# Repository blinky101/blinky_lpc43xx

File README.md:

# LPC43xx Example Project: Blinky

Simple Hello World-like blinky programs for the LPC43xx platform.
This repositories contains three blinky programs, in increasing order of complexity / abstraction level:

1. [bare-metal](/bare-metal): A blinky program in one file, with no dependencies at all.
2. [basic](/basic): A proper but very basic c program, where the low-level stuff is in separate functions.
3. [cpm](/cpm/): Using CPM as c package manager: reuseable dependencies are in separate repositories.

Extras:
* [dual_core](/dual_core/): Uses both the cortex-M4 and the cortex-M0 cores, blinking two LEDS independently.
* [cpm_bootloader](/cpm_bootloader/): Same as [cpm](/cpm/), but used in combination with a custom bootloader.

See [the blinky website](https://blinky101.github.io/blinky_lpc43xx/) and the per-project *README* files for more information.

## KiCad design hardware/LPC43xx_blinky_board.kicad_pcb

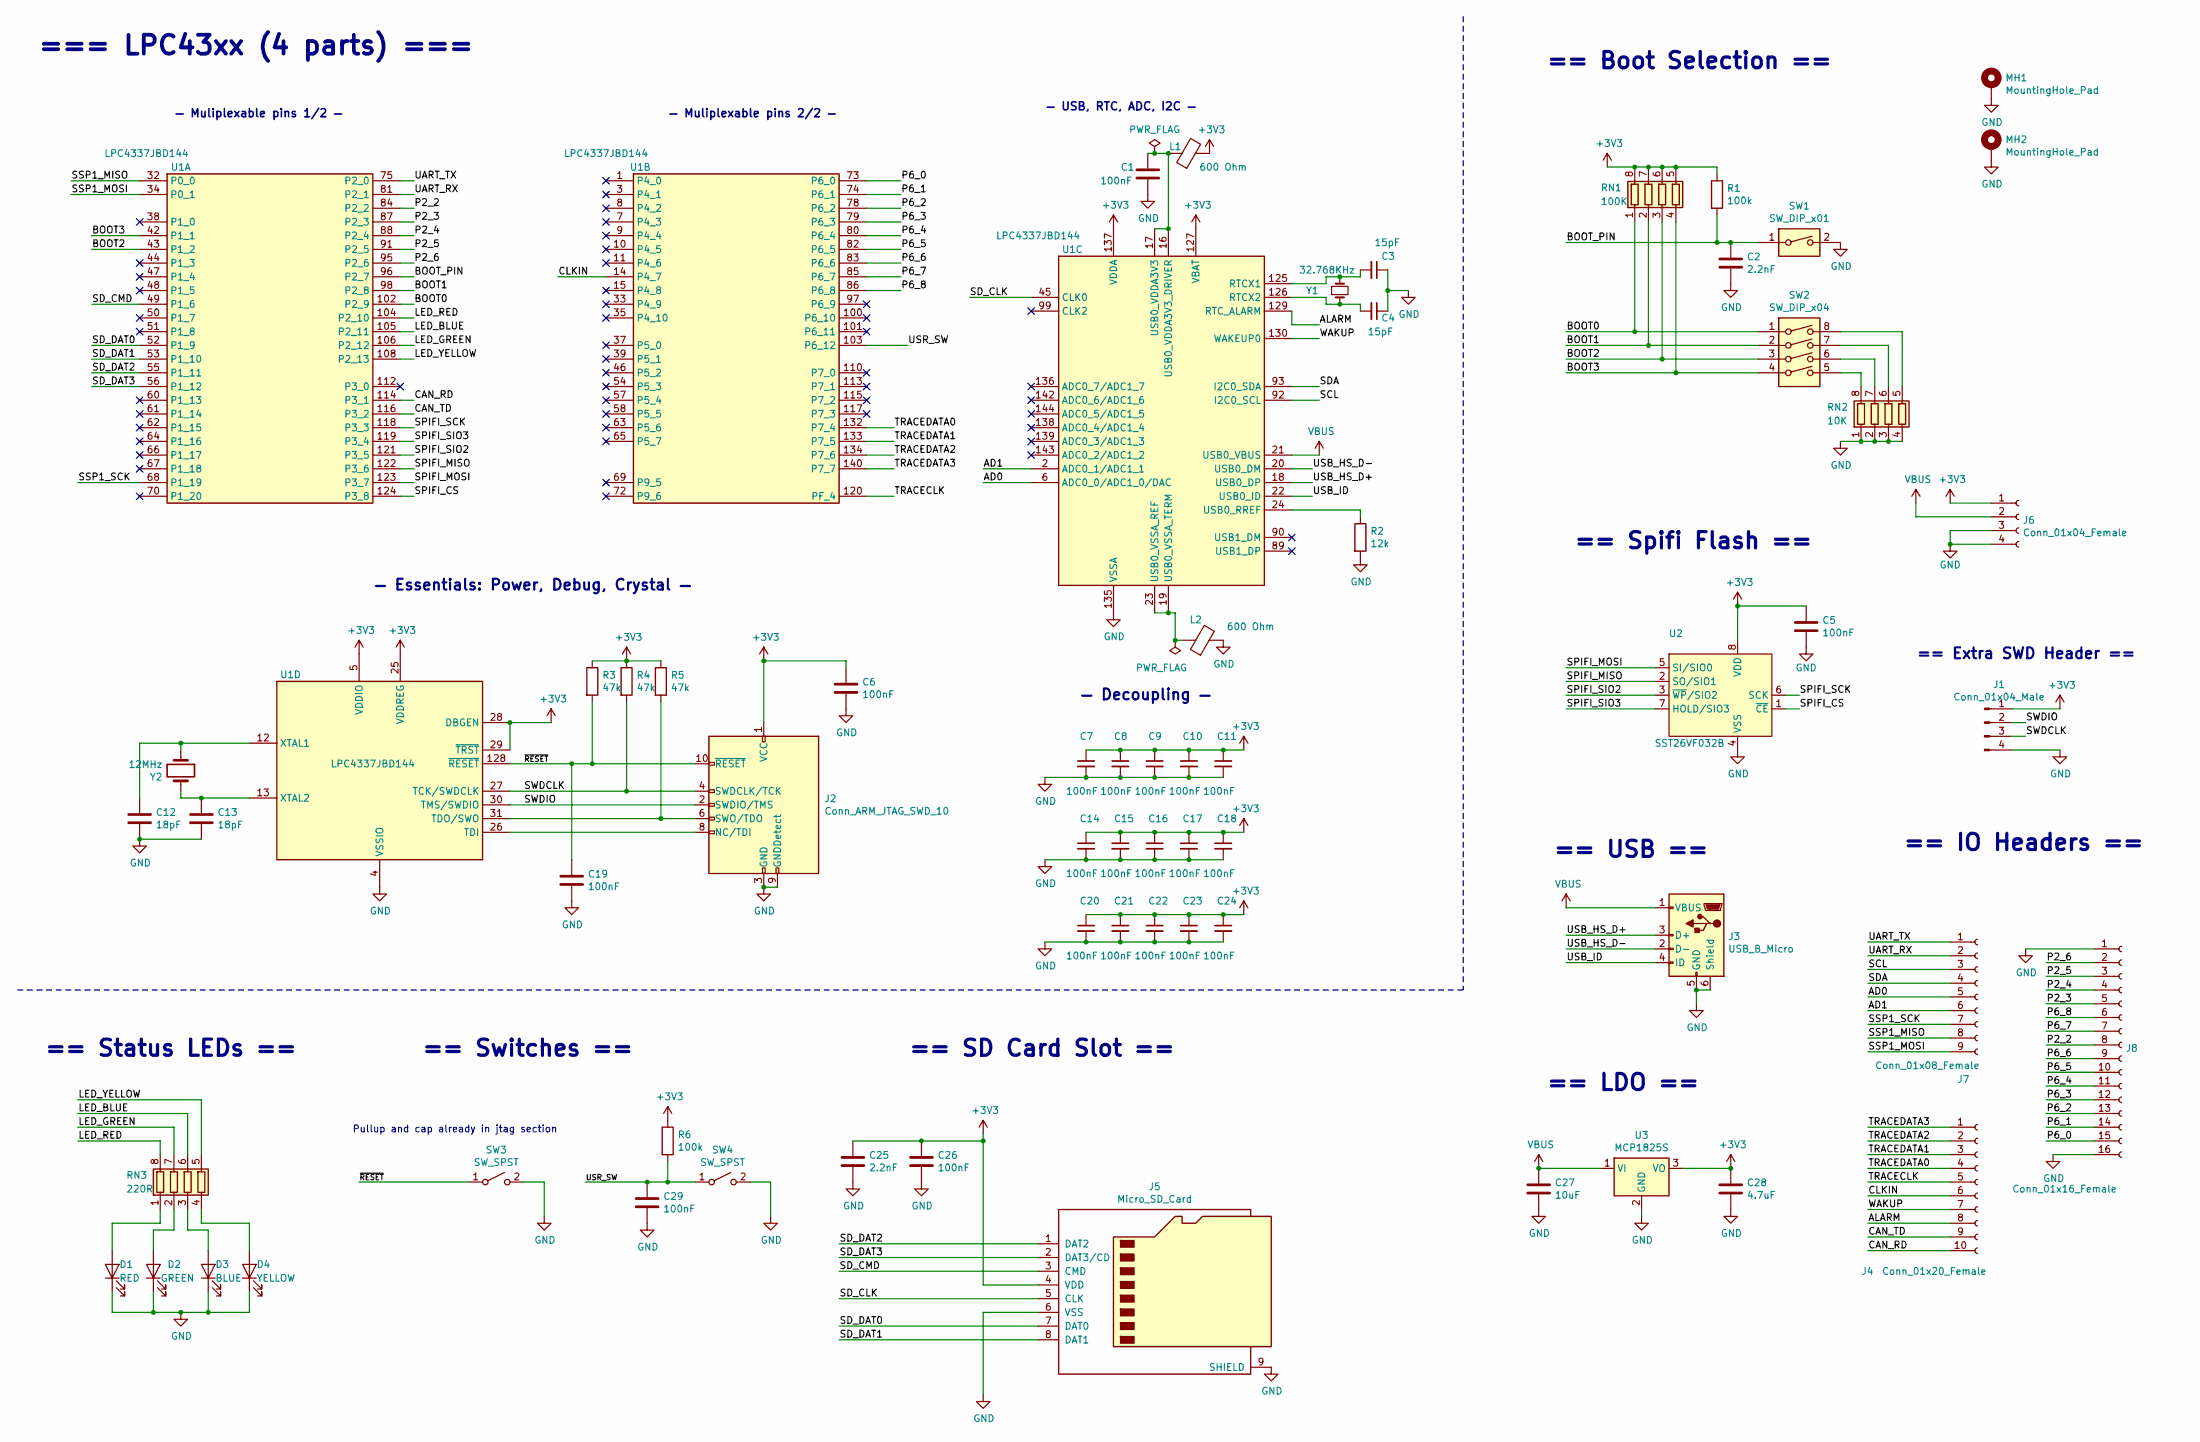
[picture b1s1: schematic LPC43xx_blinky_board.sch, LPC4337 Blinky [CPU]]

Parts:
C1, C5, C6, C7, C8, C9, C10, C11, C14, C15, C16, C17, C18, C19, C20, C21, C22, C23, C24, C26, C29: 100nF; C_0402_1005Metric
C2, C25: 2.2nF; C_0402_1005Metric
C3, C4: 15pF; C_0402_1005Metric
C12, C13: 18pF; C_0402_1005Metric
C27: 10uF; C_0805_2012Metric
C28: 4.7uF; C_0805_2012Metric
D1: RED; LED_0603_1608Metric
D2: GREEN; LED_0603_1608Metric
D3: BLUE; LED_0603_1608Metric
D4: YELLOW; LED_0603_1608Metric
J1: Conn_01x04_Male; PinHeader_1x04_P2.54mm_Horizontal
J2: Conn_ARM_JTAG_SWD_10; PinHeader_2x05_P1.27mm_Vertical_SMD
J3: USB_B_Micro; USB_Micro-B_Molex_47346-0001
J4: Conn_01x20_Female; PinSocket_1x10_P2.54mm_Vertical
J5: Micro_SD_Card; microSD_HC_Wuerth_693072010801
J6: Conn_01x04_Female; PinSocket_1x04_P2.54mm_Vertical
J7: Conn_01x08_Female; PinSocket_1x09_P2.54mm_Vertical
J8: Conn_01x16_Female; PinSocket_1x16_P2.54mm_Vertical
L1: 600 Ohm; R_0402_1005Metric
L2: 600 Ohm; R_0402_1005Metric; Manufacturer PartNo. BLM15HG601SN1D
MH1, MH2: MountingHole_Pad; MountingHole_3.2mm_M3_Pad_Via
R1, R6: 100k; R_0402_1005Metric
R2: 12k; R_0402_1005Metric
R3, R4, R5: 47k; R_0402_1005Metric
RN1: 100K; R_Array_Convex_4x0402
RN2: 10K; R_Array_Convex_4x0402
RN3: 220R; R_Array_Convex_4x0402
SW1: SW_DIP_x01; SW_DIP_SPSTx01_Slide_Omron_A6S-110x_W8.9mm_P2.54mm
SW2: SW_DIP_x04; SW_DIP_SPSTx04_Slide_Omron_A6S-410x_W8.9mm_P2.54mm
SW3, SW4: SW_SPST; SW_SPST_EVQPE1
U1: LPC4337JBD144; LQFP-144_20x20mm_P0.5mm
U2: SST26VF032B; SOIC-8_3.9x4.9mm_P1.27mm
U3: MCP1825S; SOT-223-3_TabPin2
Y1: 32.768KHz; Crystal_SMD_Abracon_ABS07-2Pin_3.6x1.9mm
Y2: 12MHz; Crystal_SMD_TXC_7A-2Pin_5.0x3.2mm

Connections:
+3V3: C5.1, C6.1, C7.1, C8.1, C9.1, C10.1, C11.1, C14.1, C15.1, C16.1, C17.1, C18.1, C20.1, C21.1, C22.1, C23.1, C24.1, C25.1, C26.1, C28.1, J1.1, J2.1 (VCC), J5.4 (VDD), J6.1, L1.2, R1.1, R3.1, R4.1, R5.1, R6.1, RN1.5 (R4.2), RN1.6 (R3.2), RN1.7 (R2.2), RN1.8 (R1.2), U1.5 (VDDIO), U1.25 (VDDREG), U1.28 (DBGEN), U1.29 (~TRST), U1.36 (VDDIO), U1.41 (VDDIO), U1.59 (VDDREG), U1.71 (VDDIO), U1.77 (VDDIO), U1.94 (VDDREG), U1.107 (VDDIO), U1.111 (VDDIO), U1.127 (VBAT), U1.131 (VDDREG), U1.137 (VDDA), U1.141 (VDDIO), U2.8 (VDD), U3.3 (VO)
/AD0: J7.5, U1.6 (ADC0_0/ADC1_0/DAC)
/AD1: J7.6, U1.2 (ADC0_1/ADC1_1)
/ALARM: J4.8, U1.129 (RTC_ALARM)
/BOOT0: RN1.1 (R1.1), SW2.1, U1.102 (P2_9)
/BOOT1: RN1.2 (R2.1), SW2.2, U1.98 (P2_8)
/BOOT2: RN1.3 (R3.1), SW2.3, U1.43 (P1_2)
/BOOT3: RN1.4 (R4.1), SW2.4, U1.42 (P1_1)
/BOOT_PIN: C2.1, R1.2, SW1.1, U1.96 (P2_7)
/CAN_RD: J4.10, U1.114 (P3_1)
/CAN_TD: J4.9, U1.116 (P3_2)
/CLKIN: J4.6, U1.14 (P4_7)
/LED_BLUE: RN3.6 (R3.2), U1.105 (P2_11)
/LED_GREEN: RN3.7 (R2.2), U1.106 (P2_12)
/LED_RED: RN3.8 (R1.2), U1.104 (P2_10)
/LED_YELLOW: RN3.5 (R4.2), U1.108 (P2_13)
/P2_2: J8.8, U1.84 (P2_2)
/P2_3: J8.5, U1.87 (P2_3)
/P2_4: J8.4, U1.88 (P2_4)
/P2_5: J8.3, U1.91 (P2_5)
/P2_6: J8.2, U1.95 (P2_6)
/P6_0: J8.15, U1.73 (P6_0)
/P6_1: J8.14, U1.74 (P6_1)
/P6_2: J8.13, U1.78 (P6_2)
/P6_3: J8.12, U1.79 (P6_3)
/P6_4: J8.11, U1.80 (P6_4)
/P6_5: J8.10, U1.82 (P6_5)
/P6_6: J8.9, U1.83 (P6_6)
/P6_7: J8.7, U1.85 (P6_7)
/P6_8: J8.6, U1.86 (P6_8)
/SCL: J7.3, U1.92 (I2C0_SCL)
/SDA: J7.4, U1.93 (I2C0_SDA)
/SD_CLK: J5.5 (CLK), U1.45 (CLK0)
/SD_CMD: J5.3 (CMD), U1.49 (P1_6)
/SD_DAT0: J5.7 (DAT0), U1.52 (P1_9)
/SD_DAT1: J5.8 (DAT1), U1.53 (P1_10)
/SD_DAT2: J5.1 (DAT2), U1.55 (P1_11)
/SD_DAT3: J5.2 (DAT3/CD), U1.56 (P1_12)
/SPIFI_CS: U1.124 (P3_8), U2.1 (~CE)
/SPIFI_MISO: U1.122 (P3_6), U2.2 (SO/SIO1)
/SPIFI_MOSI: U1.123 (P3_7), U2.5 (SI/SIO0)
/SPIFI_SCK: U1.118 (P3_3), U2.6 (SCK)
/SPIFI_SIO2: U1.121 (P3_5), U2.3 (~WP~/SIO2)
/SPIFI_SIO3: U1.119 (P3_4), U2.7 (HOLD/SIO3)
/SSP1_MISO: J7.8, U1.32 (P0_0)
/SSP1_MOSI: J7.9, U1.34 (P0_1)
/SSP1_SCK: J7.7, U1.68 (P1_19)
/SWDCLK: J1.3, J2.4 (SWDCLK/TCK), R4.2, U1.27 (TCK/SWDCLK)
/SWDIO: J1.2, J2.2 (SWDIO/TMS), U1.30 (TMS/SWDIO)
/TRACECLK: J4.5, U1.120 (PF_4)
/TRACEDATA0: J4.4, U1.132 (P7_4)
/TRACEDATA1: J4.3, U1.133 (P7_5)
/TRACEDATA2: J4.2, U1.134 (P7_6)
/TRACEDATA3: J4.1, U1.140 (P7_7)
/UART_RX: J7.2, U1.81 (P2_1)
/UART_TX: J7.1, U1.75 (P2_0)
/USB_HS_D+: J3.3 (D+), U1.18 (USB0_DP)
/USB_HS_D-: J3.2 (D-), U1.20 (USB0_DM)
/USB_ID: J3.4 (ID), U1.22 (USB0_ID)
/USR_SW: C29.1, R6.2, SW4.1 (A), U1.103 (P6_12)
/WAKUP: J4.7, U1.130 (WAKEUP0)
/~RESET: C19.1, J2.10 (~RESET~), R3.2, SW3.1 (A), U1.128 (~RESET)
GND: C1.2, C2.2, C3.1, C4.1, C5.2, C6.2, C7.2, C8.2, C9.2, C10.2, C11.2, C12.2, C13.2, C14.2, C15.2, C16.2, C17.2, C18.2, C19.2, C20.2, C21.2, C22.2, C23.2, C24.2, C25.2, C26.2, C27.2, C28.2, C29.2, D1.1 (K), D2.1 (K), D3.1 (K), D4.1 (K), J1.4, J2.3 (GND), J2.5 (GND), J2.9 (GNDDetect), J3.5 (GND), J3.6 (Shield), J5.6 (VSS), J5.9 (SHIELD), J6.3, J6.4, J8.1, J8.16, L2.2, MH1.1, MH2.1, R2.2, RN2.1 (R1.1), RN2.2 (R2.1), RN2.3 (R3.1), RN2.4 (R4.1), SW1.2, SW3.2 (B), SW4.2 (B), U1.4 (VSSIO), U1.40 (VSSIO), U1.76 (VSSIO), U1.109 (VSSIO), U1.135 (VSSA), U2.4 (VSS), U3.2 (GND)
unnamed: C1.1, L1.1, U1.16 (USB0_VDDA3V3_DRIVER), U1.17 (USB0_VDDA3V3)
unnamed: C3.2, U1.125 (RTCX1), Y1.1
unnamed: C4.2, U1.126 (RTCX2), Y1.2
unnamed: C12.1, U1.12 (XTAL1), Y2.1
unnamed: C13.1, U1.13 (XTAL2), Y2.2
unnamed: D1.2 (A), RN3.1 (R1.1)
unnamed: D2.2 (A), RN3.2 (R2.1)
unnamed: D3.2 (A), RN3.3 (R3.1)
unnamed: D4.2 (A), RN3.4 (R4.1)
unnamed: J2.6 (SWO/TDO), R5.2, U1.31 (TDO/SWO)
unnamed: J2.8 (NC/TDI), U1.26 (TDI)
unnamed: L2.1, U1.19 (USB0_VSSA_TERM), U1.23 (USB0_VSSA_REF)
unnamed: R2.1, U1.24 (USB0_RREF)
unnamed: RN2.5 (R4.2), SW2.8
unnamed: RN2.6 (R3.2), SW2.7
unnamed: RN2.7 (R2.2), SW2.6
unnamed: RN2.8 (R1.2), SW2.5
VBUS: C27.1, J3.1 (VBUS), J6.2, U1.21 (USB0_VBUS), U3.1 (VI)

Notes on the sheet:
== Boot Selection ==
— Decoupling —
— Essentials: Power, Debug, Crystal —
— USB, RTC, ADC, I2C —
== Switches ==
== Spifi Flash ==
== Status LEDs ==
== SD Card Slot ==
=== LPC43xx (4 parts) ===
— Muliplexable pins 1/2 —
— Muliplexable pins 2/2 —
== USB ==
== LDO ==
== IO Headers ==
== Extra SWD Header ==
Pullup and cap already in jtag section

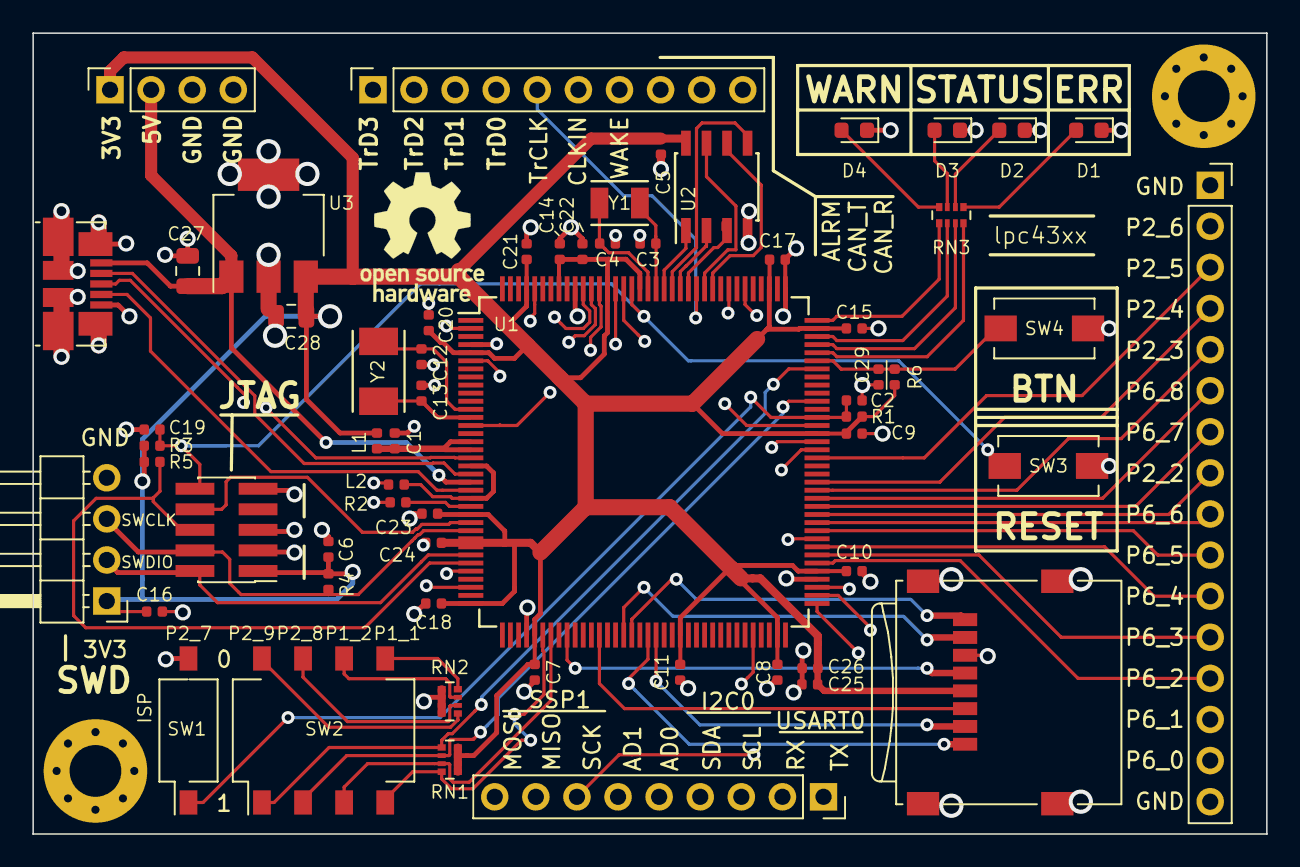
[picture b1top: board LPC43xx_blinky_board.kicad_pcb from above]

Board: 4 copper layers, 76.2 x 49.5 mm, 63 parts (0 on the bottom side), 81 nets.

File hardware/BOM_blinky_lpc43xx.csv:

,,,,,,,,,
Ref,Value,Qnty,Supplier and ref,Cmp name,Footprint,Description,Vendor,,
"C3, C4,",15pF,2,3019172,C_Small,Capacitor_SMD:C_0402_1005Metric,"Unpolarized capacitor, small symbol",,,
"C6, C2, C7, C29, C8, C9, C11, C10, C14, C15, C16, C18, C17, C20, C21, C22, C24, C23, C5, C1, C26, C19,",100nF,22,2627420,C,Capacitor_SMD:C_0402_1005Metric,Unpolarized capacitor,,,
"C13, C12,",18pF,2,2896333,C,Capacitor_SMD:C_0402_1005Metric,Unpolarized capacitor,,,
"C25,",2.2nF,1,2896351,C,Capacitor_SMD:C_0402_1005Metric,Unpolarized capacitor,,,
"C27,",10uF,1,2611941,C,Capacitor_SMD:C_0805_2012Metric,Unpolarized capacitor,,,
"C28,",4.7uF,1,9402160,C,Capacitor_SMD:C_0805_2012Metric,Unpolarized capacitor,,,
"D1,",RED,1,2322071,LED,LED_SMD:LED_0603_1608Metric,Light emitting diode,,,
"D2,",GREEN,1,2846585,LED,LED_SMD:LED_0603_1608Metric,Light emitting diode,,,
"D3,",BLUE,1,1328305,LED,LED_SMD:LED_0603_1608Metric,Light emitting diode,,,
"D4,",YELLOW,1,2103887,LED,LED_SMD:LED_0603_1608Metric,Light emitting diode,,,
"J2,",Conn_ARM_JTAG_SWD_10,1,2856426,Conn_ARM_JTAG_SWD_10,Connector_PinHeader_1.27mm:PinHeader_2x05_P1.27mm_Vertical_SMD,"Cortex Debug Connector, standard ARM Cortex-M SWD and JTAG interface",,,
"J3,",USB_B_Micro,1,1568026,USB_B_Micro,Connector_USB:USB_Micro-B_Molex_47346-0001,USB Micro Type B connector,,,
"J5,",Micro_SD_Card,1,2081364,Micro_SD_Card,Connector_Card:microSD_HC_Wuerth_693072010801,Micro SD Card Socket,,,
"L1, L2,",600 Ohm,2,2443223,Ferrite_Bead,Resistor_SMD:R_0402_1005Metric,Ferrite bead,,,
"R1, R6,",100k,2,2861833,R,Resistor_SMD:R_0402_1005Metric,Resistor,,,
"R2,",12k,1,2447104,R,Resistor_SMD:R_0402_1005Metric,Resistor,,,
"R5, R4, R3,",47k,3,2861831,R,Resistor_SMD:R_0402_1005Metric,Resistor,,,
"RN1,",100K,1,2060062,R_Pack04,Resistor_SMD:R_Array_Convex_4x0402,"4 resistor network, parallel topology, DIP package",,,
"RN2,",10K,1,2060058,R_Pack04,Resistor_SMD:R_Array_Convex_4x0402,"4 resistor network, parallel topology, DIP package",,,
"RN3,",220R,1,9235329,R_Pack04,Resistor_SMD:R_Array_Convex_4x0402,"4 resistor network, parallel topology, DIP package",,,
"SW1,",SW_DIP_x01,1,1960892,SW_DIP_x01,Button_Switch_SMD:SW_DIP_SPSTx01_Slide_Omron_A6S-110x_W8.9mm_P2.54mm,"1x DIP Switch, Single Pole Single Throw (SPST) switch, small symbol",,,
"SW2,",SW_DIP_x04,1,1960899,SW_DIP_x04,Button_Switch_SMD:SW_DIP_SPSTx04_Slide_Omron_A6S-410x_W8.9mm_P2.54mm,"4x DIP Switch, Single Pole Single Throw (SPST) switch, small symbol",,,
"SW3, SW4,",SW_SPST,2,2079522,SW_SPST,Button_Switch_SMD:SW_SPST_EVQPE1,Single Pole Single Throw (SPST) switch,,,
"U1,",LPC4337JBD144,1,2320720,LPC4337JBD144-JitterLib,Package_QFP:LQFP-144_20x20mm_P0.5mm,,,,
"U2,",SST26VF032B,1,2471177,SST26VF032B,Package_SO:SOIC-8_3.9x4.9mm_P1.27mm,Quad SPI Flash 4MB,,,
"U3,",MCP1825S,1,1578404,MCP1825S,Package_TO_SOT_SMD:SOT-223-3_TabPin2,"500 mA, Low-Voltage, Low Quiescent Current LDO Regulator, SOT-223, TO-220, TO-263",,,
"Y1,",32.768KHz,1,2101347,Crystal_Small,Jitter_Footprints:Crystal_SMD_Abracon_ABS07-2Pin_3.6x1.9mm,"Two pin crystal, small symbol",,,
"Y2,",12MHz,1,1841940,Crystal,Jitter_Footprints:Crystal_SMD_TXC_7A-2Pin_5.0x3.2mm,Two pin crystal,,,
"J1,",Conn_01x04_Male,1,,Conn_01x04_Male,Connector_PinHeader_2.54mm:PinHeader_1x04_P2.54mm_Horizontal,"Generic connector, single row, 01x04, script generated (kicad-library-utils/schlib/autogen/connector/)",,,
"J4,",Conn_01x20_Female,1,,Conn_01x10_Female,Connector_PinSocket_2.54mm:PinSocket_1x10_P2.54mm_Vertical,"Generic connector, single row, 01x10, script generated (kicad-library-utils/schlib/autogen/connector/)",,,
"J6,",Conn_01x04_Female,1,,Conn_01x04_Female,Connector_PinSocket_2.54mm:PinSocket_1x04_P2.54mm_Vertical,"Generic connector, single row, 01x04, script generated (kicad-library-utils/schlib/autogen/connector/)",,,
"J7,",Conn_01x08_Female,1,,Conn_01x09_Female,Connector_PinSocket_2.54mm:PinSocket_1x09_P2.54mm_Vertical,"Generic connector, single row, 01x09, script generated (kicad-library-utils/schlib/autogen/connector/)",,,
"J8,",Conn_01x16_Female,1,,Conn_01x16_Female,Connector_PinSocket_2.54mm:PinSocket_1x16_P2.54mm_Vertical,"Generic connector, single row, 01x16, script generated (kicad-library-utils/schlib/autogen/connector/)",,,

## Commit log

2016-08-29 First commit: simple CPM demo package
    A simple Hello World style blinky program for the LPC43xx platform
    as a CPM package.
    Only the M4 core is used. This is a very basic demo
    program to show how the library packages can be used.
    It depends on:
    * 43xx_m4_startup: startup code
2016-08-31 upgrade to openocd_tools 1.1
2016-09-01 Add CMake Toolchain file
2016-09-01 fix flash.cfg flusing
2016-09-26 Change ASM compiler from as to gcc
    This way you can use gcc switches
2016-09-26 link to system libraries, use gcc as linker
    This commit does not change how this example firmware project works,
    but makes it easier to build a more complex firmware on top of it:
    - link to libm, libc, libgcc. If you dou anything more than
    a very simple hello world program, you need this.
    - a few tweaks to the linker flags
2017-04-11 Interrupt-based version of blinky
    This version uses the systick timer interrupt instead of a blocking loop.
2017-04-11 Blinky demo: version for use with bootloader
    See the bootloader43xx_sdcard project on github for the bootloader.
2018-08-09 update dependencies to latest versions
2018-08-21 Fix cmake dependencies so that 'make flash' works
2018-08-21 Update Readme.md. add photo
2018-08-29 Add .vscode debug config
    Use with cortex-debug extension and blackmagic probe
2018-08-29 make flash and make debug should depend on make bin
2018-09-07 refactor repository: move cpm project to subdirectory
2018-09-07 add bliny101 compatible site
2018-09-07 add image of lpc43xx (lqfp 144)
2018-09-11 cpm project: do not use bootloader.
    version with bootloader is in cpm_bootloader
2018-09-11 cpm project: minor refactor, use mcu_debug package
2018-09-11 Start adding bare-metal example
    NOTE: UNDER CONSTRUCTION! The example will not work because it is not
    fully ported from the 11uxx to 43xx platform!
2018-09-11 bare-metal: code works, tutorial still under construction
2018-09-11 bare-metal: tutorial complete
2018-09-12 bare-metal: add FAQ about bmp tpwr_enable feature
2018-09-12 cpm README: add required step: create config.cmake
2018-09-12 cpm project: also toggle GPIO1[12]: compatible with ngx xplorer
2018-09-12 docs: add getting_started, update images
2018-09-12 Tutorial: add TODO note about pin number mismatch
2018-09-14 bare-metal: rewrite to use P2_12 (GPIO1_12)
    This is compatible with the xplorer board
2018-09-14 docs index: first two tutorials are available
2018-09-14 Website: add more explicit link to repository
2018-09-14 README: update to reflect that bare-metal is now implemented
2018-09-14 cpm projects: update README, remove obsolete image
2018-09-14 Update README.md
    remove obsolete reference to our 'custom board'
2018-09-18 Add 'basic' project
2018-09-20 CPM projects: update libraries
2018-09-24 tutorial: part 2 is no longer 'under construction'
2018-09-24 CPM projects: move cmake files to subfolder
2018-09-24 tutorial: add part 3
2018-09-24 Update index.md
    fix typo
2018-09-24 Add Kicad files. Blinky board still work in progress.
2018-09-24 Add Spifi Flash to lib and schematics
2018-09-24 Add status leds and SD Card
2018-09-25 Add headers with some selected useful pins to schematics
    During routing pinswapping might still be desirable.
2018-09-25 All footprints are assigned. Ready for layout.
2018-09-26 Starting layout work for blinky board
2018-09-28 cpm: update board_config to use lpc_tools
2018-09-28 cpm: update cmakelists to enable floating point support
2018-09-28 Add example project 'dual_core'
    The dual core project blinks two LEDs: the M4 core blinks one LED, while
    the M0 core blinks the other one.
    This is an updated version of the project at https://github.com/JitterCompany/example_blinky_lpc43xx_dual_core.
    It still needs some further updates. TODOS:
    * Add a README
    * Update pin numbers to match the correct LEDS
2018-10-04 'dual_core' project: update board config logic + pin numbers
2018-10-04 cpm + dual_core project: update README
2018-10-04 Add warnings about powering via JTAG connector
2018-10-04 Routed the left side of the board
    - USB
    - JTAG
    - Crystals
2018-10-04 Finish routing except random IO headers
2018-10-04 Route all missing connections
2018-10-04 Add final header and silkscreen
2018-10-04 Add missing step files and fix some milimeter work
2018-10-04 Some silkscreen fixes
2018-10-09 Update README overview: add dual_core
2018-10-09 Update tutorial part 3: link to dual core tutorial
2018-10-09 Create dual-core tutorial
2018-10-09 Add dual core tutorial to index.md
2018-10-16 Use custom footprints from new Jitter Kicad Libs
2018-10-17 Move 3D shapes to external library. Add renders
2018-10-19 Fix grid and move two caps out of sd card area
2018-10-26 PCB design: small adjustments according to pre-order checklist
2018-10-26 Hardware: fix schematics library reference + connect mounting hoe to GND
2018-10-26 Hardware: adjust pcb desigh according to checklist
2018-10-26 Hardware: Finish panel design
2018-10-26 Add Bill Of Materials
2018-10-26 Add supplier part numbers to BOM
2019-02-27 Update pcb: connect usb_vbus
    USB_VBUS is needed for USB BOOT ROM.
    ISP switch capacitor decreased to 2.2nF. 100nF was to high/slow for
    power up to ISP mode
